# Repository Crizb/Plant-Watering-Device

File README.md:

# Plant Watering Device with HTML server Capabilities

Another simple device which was made to test capabilities of NodeMCU ESP8266, and displaying informations on HTML Server through WI-Fi.

So to start simply. I wanted to monitor the condition of plants in my house and to make myself sure that they won't die if I forget to water them everyday.
I used some soil Humidity sensors to measure the ground and water level sensors to measure how much water is left in the water bottle which was supplying water to the pumps. 

This project was not meant to be professional. It was just a test of NodeMcu ESP8266 and it's capabilities to create a remote Wi-Fi monitor.

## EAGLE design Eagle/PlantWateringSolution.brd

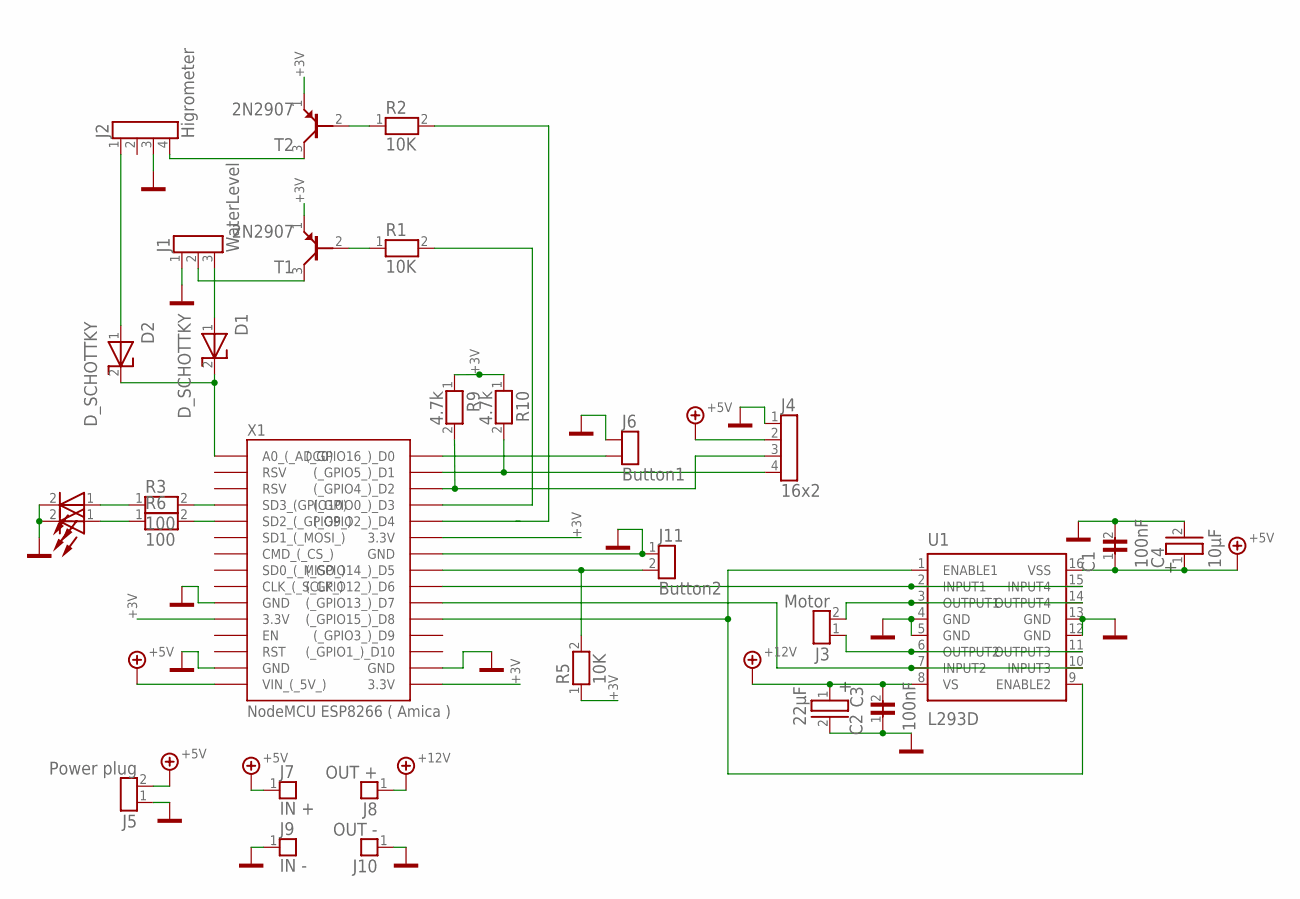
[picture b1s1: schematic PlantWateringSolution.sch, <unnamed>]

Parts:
C1: 100nF; 6X6R2,54_DISC_18
C2: 100nF; 6X6R2,54_DISC_19
C3: 22µF; D6R2,54_ELKO_20
C4: 10µF; D6R2,54_ELKO_21
D1: D_SCHOTTKY; DO35_5
D2: D_SCHOTTKY; DO35_6
D3: HLMA-KH00; LED_3MM_RED_47
D4: HLMA-KH00; LED_3MM_RED_42
J1: WaterLevel; STIFTLEISTE_1X03_G_2,54_2
J2: Higrometer; STIFTLEISTE_1X04_G_2,54_3
J3: Motor; STIFTLEISTE_1X02_G_2,54_4
J4: 16x2; STIFTLEISTE_1X04_G_2,54_43
J5: Power plug; STIFTLEISTE_1X02_G_2,54_50
J7: IN +; STIFTLEISTE_1X01_G_2,54_32
J8: OUT +; STIFTLEISTE_1X01_G_2,54_33
J9: IN -; STIFTLEISTE_1X01_G_2,54_34
J10: OUT -; STIFTLEISTE_1X01_G_2,54_35
J11: Button2; STIFTLEISTE_1X02_G_2,54_53
R1: 10K; 0204_MET_9
R2: 10K; 0204_MET_10
R3: 100; 0204_MET_46
R5: 10K; 0204_MET_31
R6: 100; 0204_MET_41
R9: 4.7k; 0204_MET_55
R10: 4.7k; 0204_MET_56
T1: 2N2907; TO18_7
T2: 2N2907; TO18_8
U1: L293D; DIL16_1
X1: NodeMCU ESP8266 ( Amica ); NODEMCU_ESP8266_DEV_0

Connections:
1: R2.1, T2.2 (B)
(_GPIO16_)_D0: X1.30 ((_GPIO16_)_D0)
+3V: R5.1, R9.1, R10.1, T1.1 (E), T2.1 (E), X1.11 (3.3V), X1.16 (3.3V), X1.25 (3.3V)
+5V: C1.1, C4.1 (+), J4.2, J5.2, J7.1, U1.16 (VSS), X1.15 (VIN_(_5V_))
+12V: C2.2, C3.1 (+), J8.1, U1.8 (VS)
A: D3.1 (A), R3.1
B: R1.1, T1.2 (B)
BUTTON3: J11.2, R5.2, X1.23 ((_GPIO14_)_D5)
ENABLE: U1.1 (ENABLE1), U1.9 (ENABLE2), X1.20 ((_GPIO15_)_D8)
GND: C1.2, C2.1, C3.2 (-), C4.2 (-), D3.2 (K), D4.2 (K), J1.1, J2.3, J4.1, J5.1, J9.1, J10.1, J11.1, U1.4 (GND), U1.5 (GND), U1.12 (GND), U1.13 (GND), X1.10 (GND), X1.14 (GND), X1.17 (GND), X1.24 (GND)
HIGROMETER_SIG: D2.1 (A), J2.1
HIGROMETER_VIN: J2.4, T2.3 (C)
INPUT1: U1.2 (INPUT1), U1.15 (INPUT4), X1.22 ((_GPIO12_)_D6)
INPUT2: U1.7 (INPUT2), U1.10 (INPUT3), X1.21 ((_GPIO13_)_D7)
K: D1.2 (K), D2.2 (K), X1.1 (A0_(_ADC0))
OUTPUT1: J3.2, U1.3 (OUTPUT1), U1.14 (OUTPUT4)
OUTPUT2: J3.1, U1.6 (OUTPUT2), U1.11 (OUTPUT3)
SCL: J4.4, R10.2, X1.29 ((_GPIO5_)_D1)
SD2_(_GPIO9_): R6.2, X1.5 (SD2_(_GPIO9_))
SDA: J4.3, R9.2, X1.28 ((_GPIO4_)_D2)
SIG$127: D4.1 (A), R6.1
SIG$131: R3.2, X1.4 (SD3_(GPIO10))
SIG$151: J1.2, T1.3 (C)
SIG$155: R2.2, X1.26 ((_GPIO2_)_D4)
WATERLEVEL_PNP: R1.2, X1.27 ((_GPIO0_)_D3)
WATERLEVEL_SIG: D1.1 (A), J1.3

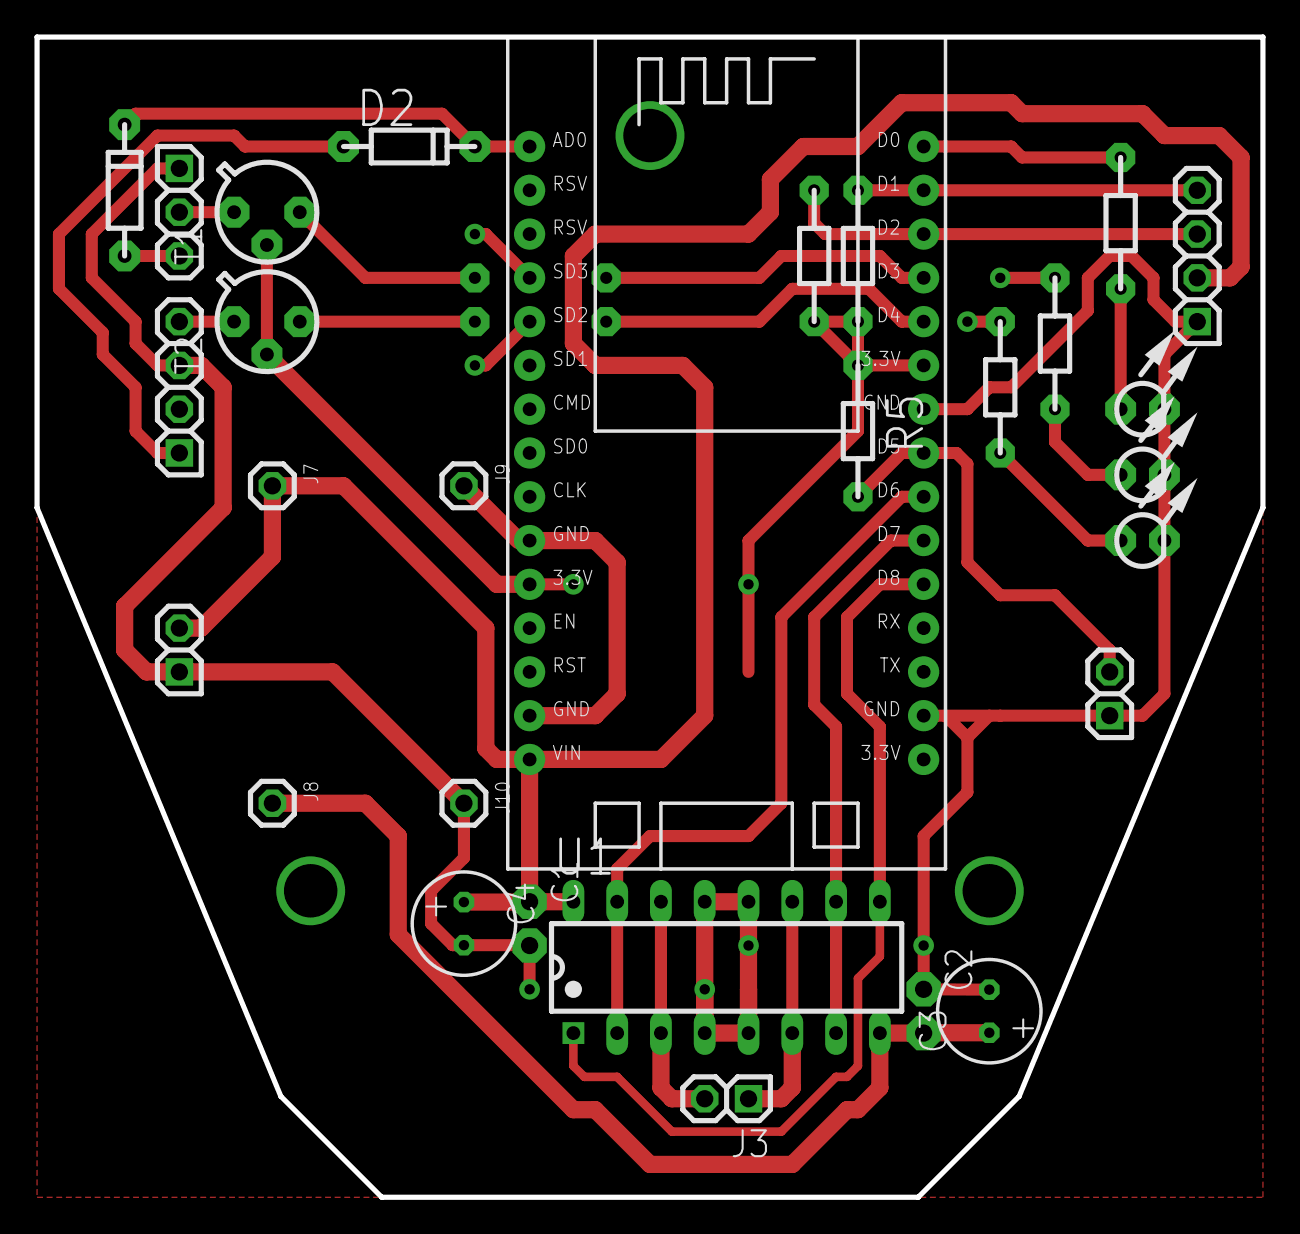
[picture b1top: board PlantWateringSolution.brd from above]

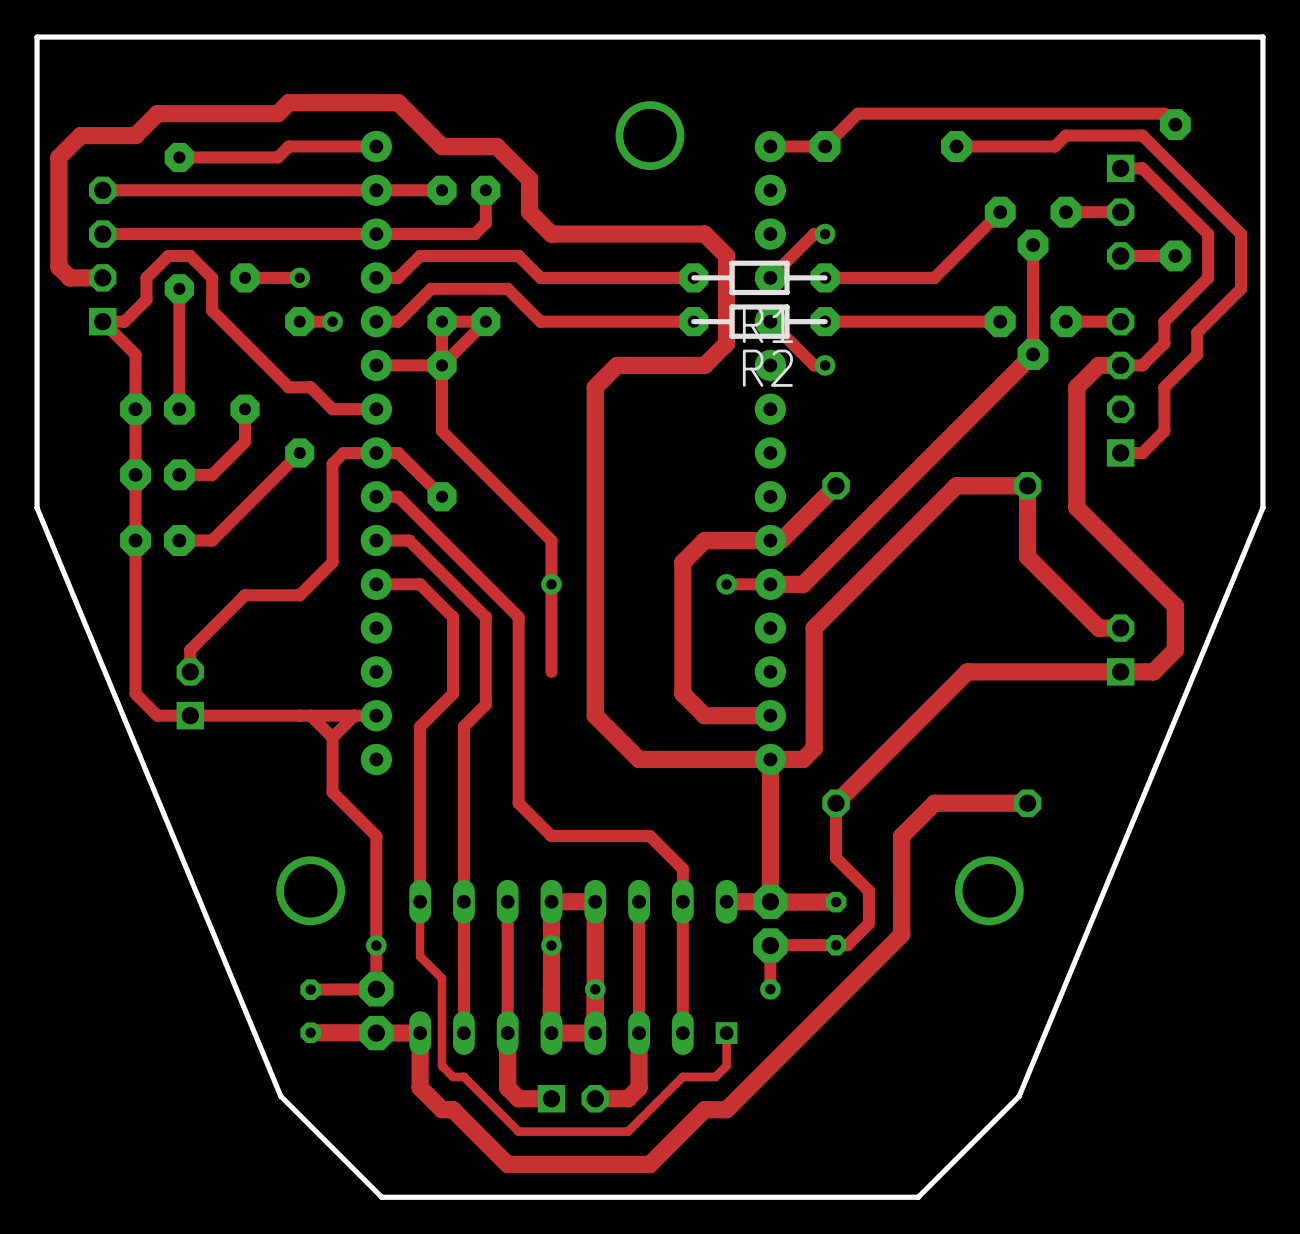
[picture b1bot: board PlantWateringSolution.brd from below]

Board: 2 copper layers, 71.1 x 67.3 mm, 31 parts (2 on the bottom side), 25 nets.

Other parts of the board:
D5: HLMA-KH00; LED_3MM_RED_49
R4: 100; 0204_MET_48

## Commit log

2020-08-12 Eagle Board and Schematic File
2020-08-12 Pictures of Schematic and Board to preview
2020-08-12 Simple testing Arduino Code
